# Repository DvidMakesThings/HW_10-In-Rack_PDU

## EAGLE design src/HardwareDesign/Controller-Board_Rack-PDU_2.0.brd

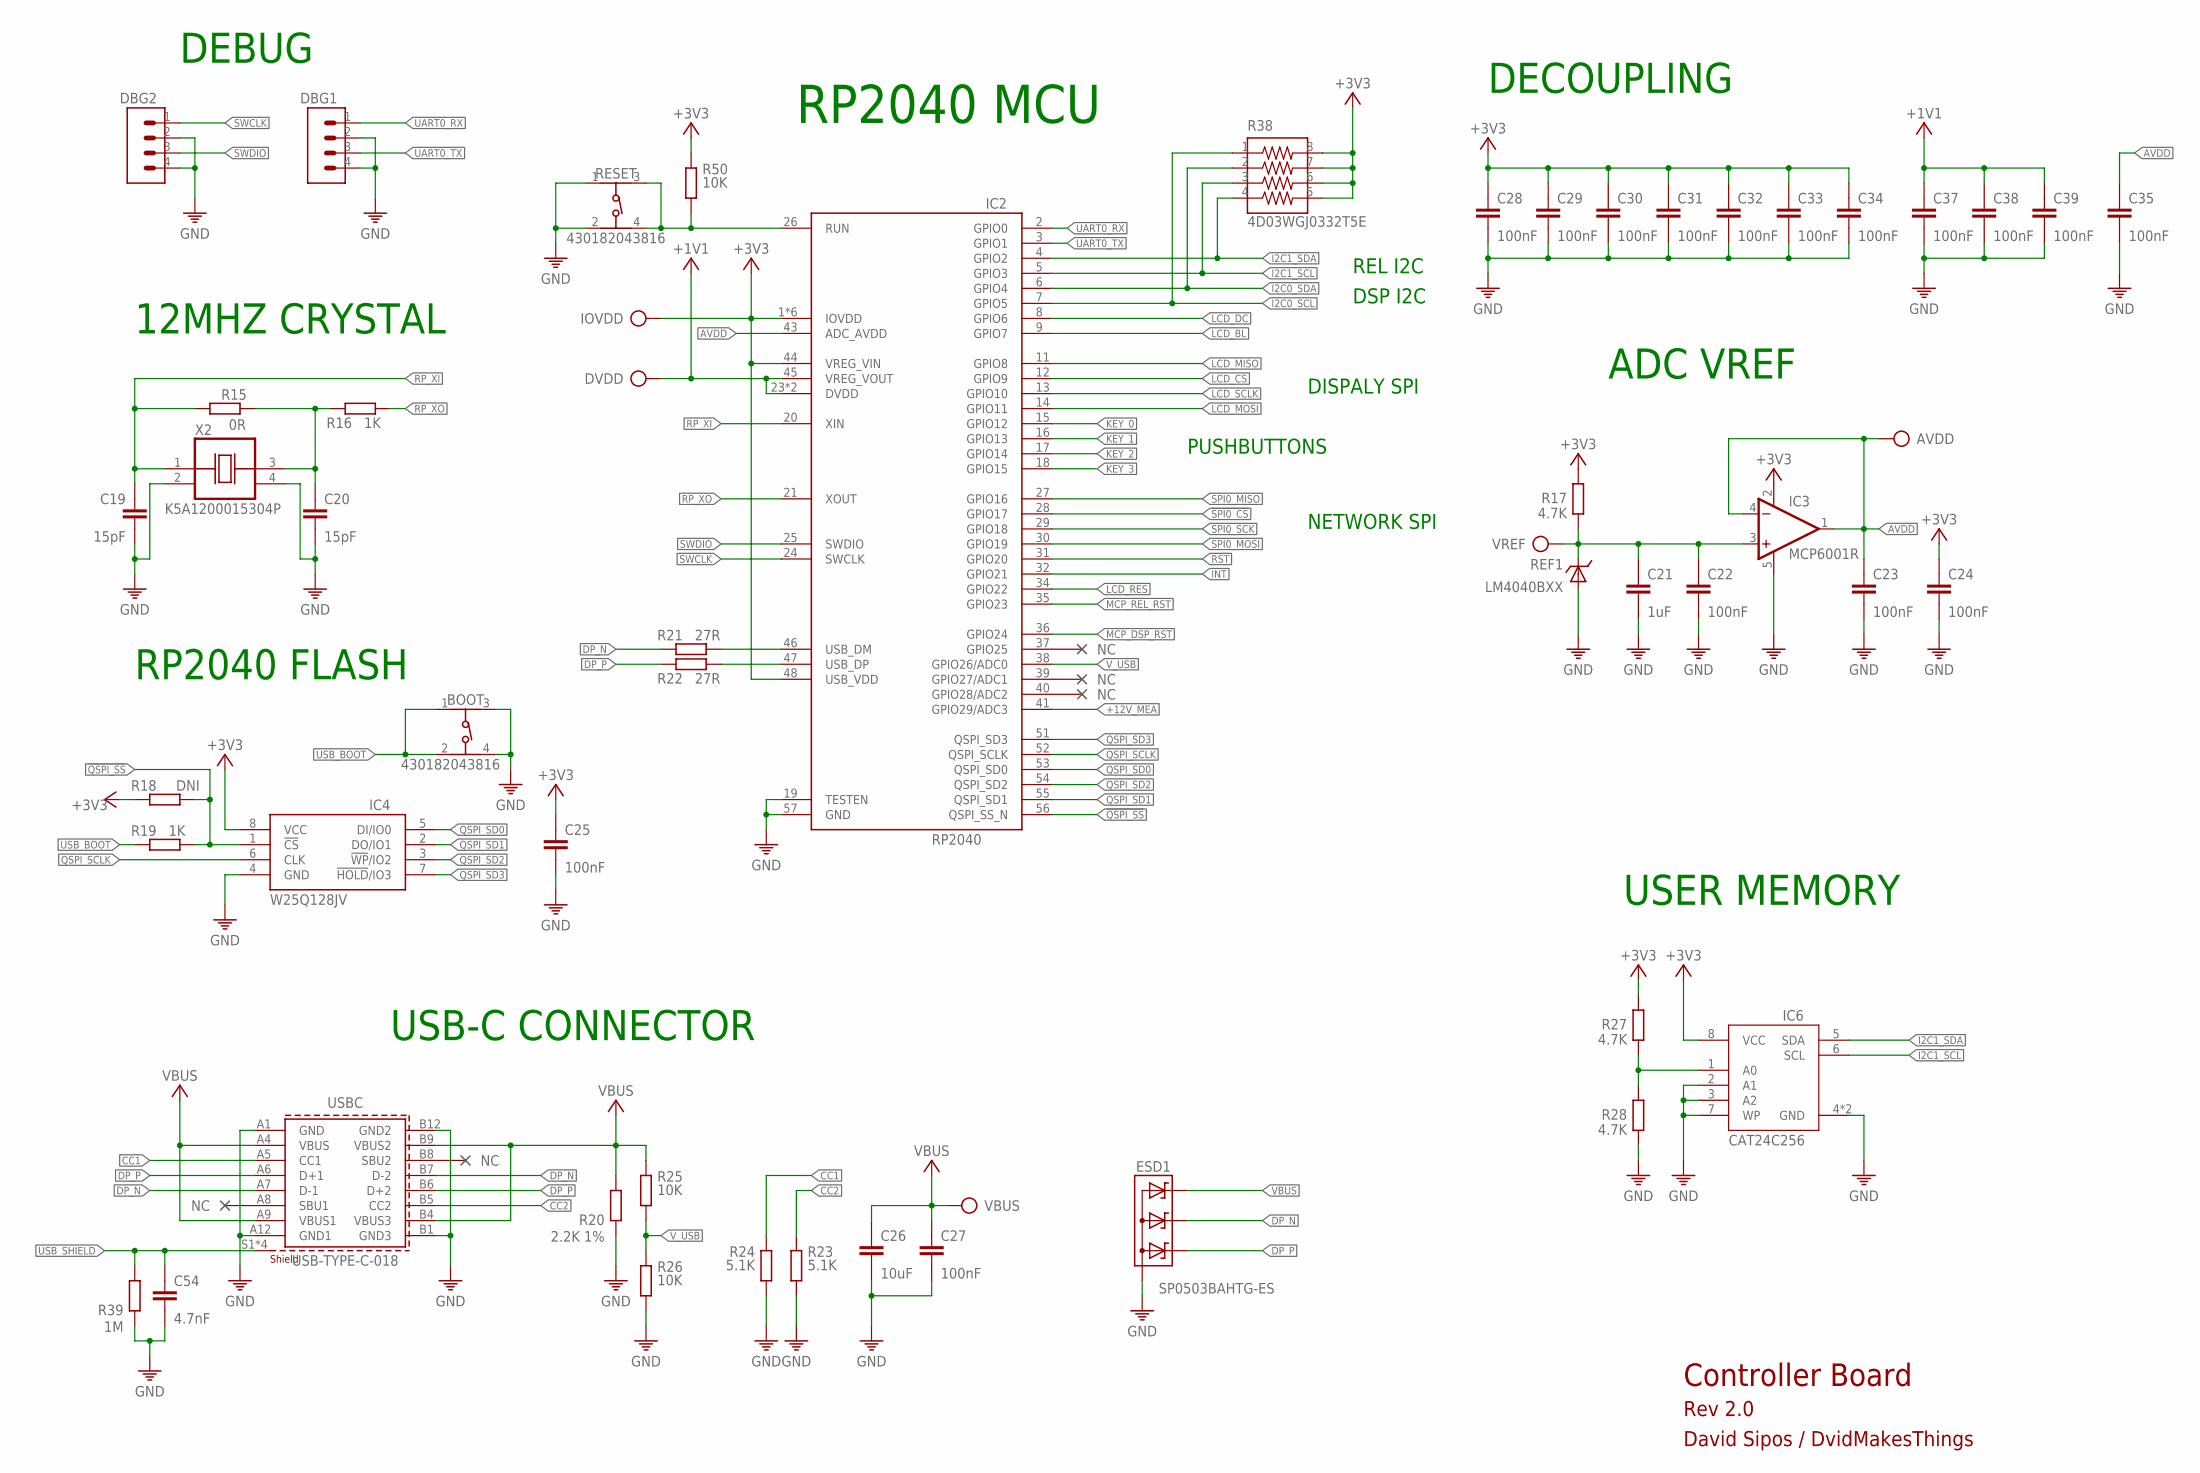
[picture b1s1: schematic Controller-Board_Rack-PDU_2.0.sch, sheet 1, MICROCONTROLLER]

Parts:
AVDD: TP
BOOT: 430182043816
C19, C20: 15pF; C0402
C21: 1uF; C0402
C22, C23, C24, C25, C28, C29, C30, C31, C32, C33, C34, C35, C37, C38, C39: 100nF; C0402
C26: 10uF; 0805
C27: 100nF; 0402
C54: 4.7nF; 0402
DBG1, DBG2: CON-1X4; 1X4
DVDD: TP
ESD1: SP0503BAHTG-ES; SOT143
IC2: RP2040; QFN40P700X700X100-57T510
IC3: MCP6001R; SOT23-5
IC4: W25Q128JVPIQ; SON127P600X500X75-8N
IC6: CAT24C256HU4IGT3; SON50P300X200X50-9T130X140N
IOVDD: TP
R15: 0R; 0402
R16, R19: 1K; 0402
R17, R27, R28: 4.7K; 0402
R18: DNI; 0402
R20: 2.2K 1%; 0402
R21, R22: 27R; 0402
R23, R24: 5.1K; 0402
R25, R26, R50: 10K; 0402
R38: 4D03WGJ0332T5E; 742C083103JP
R39: 1M; 0402
REF1: LM4040BXX; SOT23
RESET: 430182043816
USBC: USB-TYPE-C-018; 629722000214
VBUS: TP
VREF: TP
X2: K5A1200015304P; OSCCC500X320X130

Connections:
!INT: IC2.32 (GPIO21); also elsewhere on the board
!QSPI_SS: IC2.56 (QSPI_SS_N), IC4.1 (!CS), R18.1, R19.2
!RST: IC2.31 (GPIO20); also elsewhere on the board
!SPI0_CS: IC2.28 (GPIO17); also elsewhere on the board
+1V1: C37.1, C38.1, C39.1, DVDD.TP, IC2.23 (DVDD), IC2.45 (VREG_VOUT), IC2.50 (DVDD)
+3V3: C24.1, C25.1, C28.1, C29.1, C30.1, C31.1, C32.1, C33.1, C34.1, IC2.1 (IOVDD), IC2.10 (IOVDD), IC2.22 (IOVDD), IC2.33 (IOVDD), IC2.42 (IOVDD), IC2.44 (VREG_VIN), IC2.48 (USB_VDD), IC2.49 (IOVDD), IC3.2 (V+), IC4.8 (VCC), IC6.8 (VCC), IOVDD.TP, R17.2, R18.2, R27.2, R38.5, R38.6, R38.7, R38.8, R50.1; also elsewhere on the board
+12V_MEA: IC2.41 (GPIO29/ADC3); also elsewhere on the board
AVDD: AVDD.TP, C23.1, C35.1, IC2.43 (ADC_AVDD), IC3.1 (OUT), IC3.4 (-IN)
CC1: R24.1, USBC.A5 (CC1)
CC2: R23.1, USBC.B5 (CC2)
DP_N: ESD1.3 (C2), R21.1, USBC.A7 (D-1), USBC.B7 (D-2)
DP_P: ESD1.2 (C1), R22.1, USBC.A6 (D+1), USBC.B6 (D+2)
GND: BOOT.3, BOOT.4, C19.2, C20.2, C21.2, C22.2, C23.2, C24.2, C25.2, C26.2, C27.2, C28.2, C29.2, C30.2, C31.2, C32.2, C33.2, C34.2, C35.2, C37.2, C38.2, C39.2, C54.2, DBG1.2, DBG1.4, DBG2.2, DBG2.4, ESD1.1 (A), IC2.19 (TESTEN), IC2.57 (GND), IC3.5 (V-), IC4.4 (GND), IC6.2 (A1), IC6.3 (A2), IC6.4 (GND), IC6.7 (WP), IC6.9 (GND), R20.2, R23.2, R24.2, R26.2, R28.1, R39.2, REF1.2 (A), REF1.3 (A), RESET.1, RESET.2, USBC.A1 (GND), USBC.A12 (GND1), USBC.B1 (GND3), USBC.B12 (GND2), X2.2 (VSS), X2.4 (VDD); also elsewhere on the board
I2C0_SCL: IC2.7 (GPIO5), R38.1; also elsewhere on the board
I2C0_SDA: IC2.6 (GPIO4), R38.2; also elsewhere on the board
I2C1_SCL: IC2.5 (GPIO3), IC6.6 (SCL), R38.3; also elsewhere on the board
I2C1_SDA: IC2.4 (GPIO2), IC6.5 (SDA), R38.4; also elsewhere on the board
KEY_0: IC2.15 (GPIO12); also elsewhere on the board
KEY_1: IC2.16 (GPIO13); also elsewhere on the board
KEY_2: IC2.17 (GPIO14); also elsewhere on the board
KEY_3: IC2.18 (GPIO15); also elsewhere on the board
LCD_BL: IC2.9 (GPIO7); also elsewhere on the board
LCD_CS: IC2.12 (GPIO9); also elsewhere on the board
LCD_DC: IC2.8 (GPIO6); also elsewhere on the board
LCD_MISO: IC2.11 (GPIO8); also elsewhere on the board
LCD_MOSI: IC2.14 (GPIO11); also elsewhere on the board
LCD_RES: IC2.34 (GPIO22); also elsewhere on the board
LCD_SCLK: IC2.13 (GPIO10); also elsewhere on the board
MCP_DSP_RST: IC2.36 (GPIO24); also elsewhere on the board
MCP_REL_RST: IC2.35 (GPIO23); also elsewhere on the board
unnamed: C20.1, R15.2, R16.1, X2.3 (OUT)
unnamed: IC2.26 (RUN), R50.2, RESET.3, RESET.4
unnamed: IC6.1 (A0), R27.1, R28.2
QSPI_SCLK: IC2.52 (QSPI_SCLK), IC4.6 (CLK)
QSPI_SD0: IC2.53 (QSPI_SD0), IC4.5 (DI/IO0)
QSPI_SD1: IC2.55 (QSPI_SD1), IC4.2 (DO/IO1)
QSPI_SD2: IC2.54 (QSPI_SD2), IC4.3 (!WP!/IO2)
QSPI_SD3: IC2.51 (QSPI_SD3), IC4.7 (!HOLD!/IO3)
RP_XI: C19.1, IC2.20 (XIN), R15.1, X2.1 (CON)
RP_XO: IC2.21 (XOUT), R16.2
SPI0_MISO: IC2.27 (GPIO16); also elsewhere on the board
SPI0_MOSI: IC2.30 (GPIO19); also elsewhere on the board
SPI0_SCK: IC2.29 (GPIO18); also elsewhere on the board
SWCLK: DBG2.1, IC2.24 (SWCLK)
SWDIO: DBG2.3, IC2.25 (SWDIO)
UART0_RX: DBG1.1, IC2.2 (GPIO0); also elsewhere on the board
UART0_TX: DBG1.3, IC2.3 (GPIO1); also elsewhere on the board
USB_BOOT: BOOT.1, BOOT.2, R19.1
USB_DP_N: IC2.46 (USB_DM), R21.2
USB_DP_P: IC2.47 (USB_DP), R22.2
USB_SHIELD: C54.1, R39.1, USBC.S1 (SHIELD), USBC.S2 (SHIELD), USBC.S3 (SHIELD), USBC.S4 (SHIELD)
VBUS: C26.1, C27.1, ESD1.4 (C3), R20.1, R25.1, USBC.A4 (VBUS), USBC.A9 (VBUS1), USBC.B4 (VBUS3), USBC.B9 (VBUS2), VBUS.TP; also elsewhere on the board
VREF: C21.1, C22.1, IC3.3 (+IN), R17.1, REF1.1 (C), VREF.TP
V_USB: IC2.38 (GPIO26/ADC0), R25.2, R26.1

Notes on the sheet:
USB-C CONNECTOR
DECOUPLING
12MHZ CRYSTAL
RP2040 MCU
RP2040 FLASH
USER MEMORY
ADC VREF
DEBUG
Controller Board
Rev 2.0
David Sipos / DvidMakesThings
DISPALY SPI
NETWORK SPI
PUSHBUTTONS
REL I2C
DSP I2C

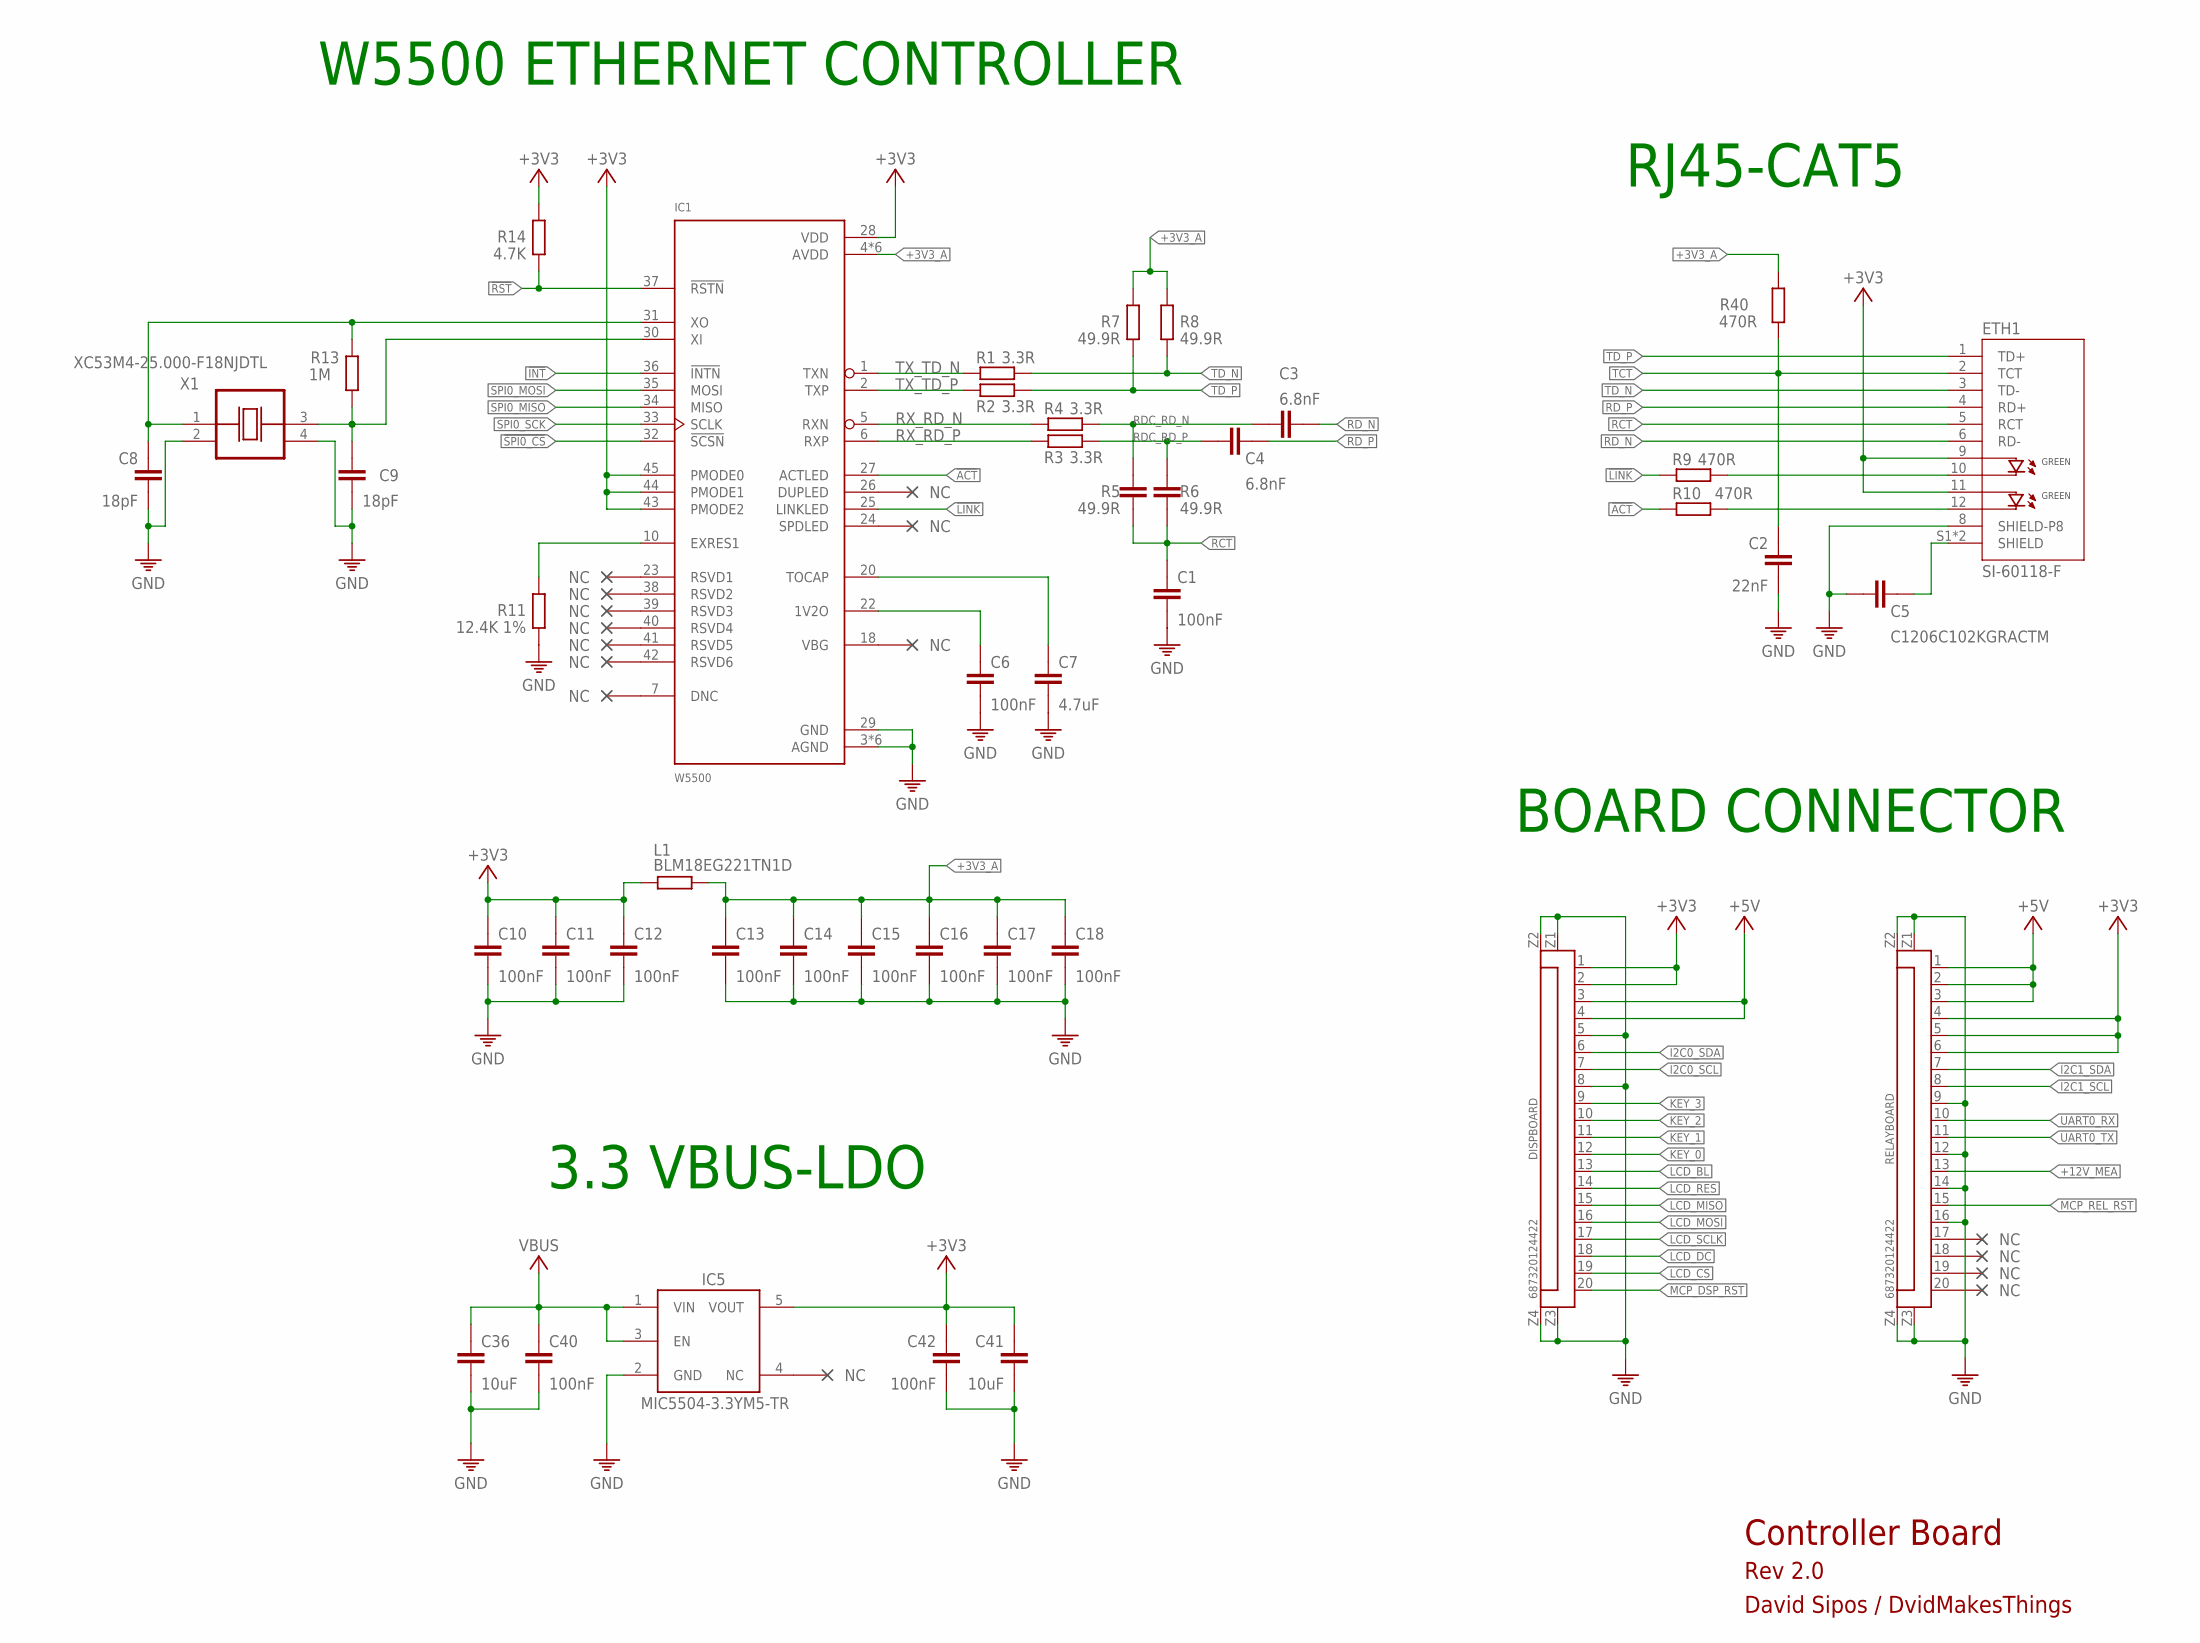
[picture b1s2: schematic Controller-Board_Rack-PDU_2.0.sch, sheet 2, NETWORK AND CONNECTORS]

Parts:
C1, C6, C10, C11, C12, C13, C14, C15, C16, C17, C18: 100nF; C0402
C2: 22nF; C0402
C3, C4: 6.8nF; C0402
C5: C1206C102KGRACTM; C1206
C7: 4.7uF; C0402
C8, C9: 18pF; C0402
C36, C41: 10uF; 0805
C40, C42: 100nF; 0402
DISPBOARD: 687320124422
ETH1: SI-60118-F; RJ45-CAT5
IC1: W5500; LQFP48
IC5: MIC5504-3.3YM5-TR; SOT23-5
L1: BLM18EG221TN1D; 0603
R1, R2, R3, R4: 3.3R; 0402
R5, R6: 49.9R; C0402
R7, R8: 49.9R; 0402
R9, R10, R40: 470R; 0402
R11: 12.4K 1%; 0402
R13: 1M; 0402
R14: 4.7K; 0402
RELAYBOARD: 687320124422
X1: XC53M4-25.000-F18NJDTL; OSCCC500X320X130

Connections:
!ACT: IC1.27 (ACTLED), R10.1
!INT: IC1.36 (!INTN); also elsewhere on the board
!LINK: IC1.25 (LINKLED), R9.1
!RST: IC1.37 (!RSTN), R14.1; also elsewhere on the board
!SPI0_CS: IC1.32 (!SCSN); also elsewhere on the board
+3V3: C10.1, C11.1, C12.1, C41.1, C42.1, DISPBOARD.1, DISPBOARD.2, ETH1.9 (GA1), ETH1.11 (GA2), IC1.28 (VDD), IC1.43 (PMODE2), IC1.44 (PMODE1), IC1.45 (PMODE0), IC5.5 (VOUT), L1.1, R14.2, RELAYBOARD.4, RELAYBOARD.5, RELAYBOARD.6; also elsewhere on the board
+3V3_A: C13.1, C14.1, C15.1, C16.1, C17.1, C18.1, IC1.4 (AVDD), IC1.8 (AVDD), IC1.11 (AVDD), IC1.15 (AVDD), IC1.17 (AVDD), IC1.21 (AVDD), L1.2, R7.2, R8.2, R40.2
+5V: DISPBOARD.3, DISPBOARD.4, RELAYBOARD.1, RELAYBOARD.2, RELAYBOARD.3
+12V_MEA: RELAYBOARD.13; also elsewhere on the board
CHASSIS: C5.2, ETH1.S1 (SHIELD), ETH1.S2 (SHIELD)
GND: C1.2, C2.2, C5.1, C6.2, C7.2, C8.2, C9.2, C10.2, C11.2, C12.2, C13.2, C14.2, C15.2, C16.2, C17.2, C18.2, C36.2, C40.2, C41.2, C42.2, DISPBOARD.5, DISPBOARD.8, DISPBOARD.Z1, DISPBOARD.Z2, DISPBOARD.Z3, DISPBOARD.Z4, ETH1.8 (SHIELD-P8), IC1.3 (AGND), IC1.9 (AGND), IC1.14 (AGND), IC1.16 (AGND), IC1.19 (AGND), IC1.29 (GND), IC1.48 (AGND), IC5.2 (GND), R11.1, RELAYBOARD.9, RELAYBOARD.12, RELAYBOARD.14, RELAYBOARD.16, RELAYBOARD.Z1, RELAYBOARD.Z2, RELAYBOARD.Z3, RELAYBOARD.Z4, X1.2 (VSS), X1.4 (VDD); also elsewhere on the board
I2C0_SCL: DISPBOARD.7; also elsewhere on the board
I2C0_SDA: DISPBOARD.6; also elsewhere on the board
I2C1_SCL: RELAYBOARD.8; also elsewhere on the board
I2C1_SDA: RELAYBOARD.7; also elsewhere on the board
KEY_0: DISPBOARD.12; also elsewhere on the board
KEY_1: DISPBOARD.11; also elsewhere on the board
KEY_2: DISPBOARD.10; also elsewhere on the board
KEY_3: DISPBOARD.9; also elsewhere on the board
LCD_BL: DISPBOARD.13; also elsewhere on the board
LCD_CS: DISPBOARD.19; also elsewhere on the board
LCD_DC: DISPBOARD.18; also elsewhere on the board
LCD_MISO: DISPBOARD.15; also elsewhere on the board
LCD_MOSI: DISPBOARD.16; also elsewhere on the board
LCD_RES: DISPBOARD.14; also elsewhere on the board
LCD_SCLK: DISPBOARD.17; also elsewhere on the board
MCP_DSP_RST: DISPBOARD.20; also elsewhere on the board
MCP_REL_RST: RELAYBOARD.15; also elsewhere on the board
unnamed: IC1.10 (EXRES1), R11.2
unnamed: ETH1.10 (GK1), R9.2
unnamed: ETH1.12 (GK2), R10.2
unnamed: C6.1, IC1.22 (1V2O)
unnamed: C7.1, IC1.20 (TOCAP)
unnamed: C9.1, IC1.30 (XI), R13.1, X1.3 (OUT)
RCT: C1.1, ETH1.5 (RCT), R5.1, R6.1
RDC_RD_N: C3.1, R4.2, R5.2
RDC_RD_P: C4.1, R3.2, R6.2
RD_N: C3.2, ETH1.6 (RD-)
RD_P: C4.2, ETH1.4 (RD+)
RX_RD_N: IC1.5 (RXN), R4.1
RX_RD_P: IC1.6 (RXP), R3.1
SPI0_MISO: IC1.34 (MISO); also elsewhere on the board
SPI0_MOSI: IC1.35 (MOSI); also elsewhere on the board
SPI0_SCK: IC1.33 (SCLK); also elsewhere on the board
TCT: C2.1, ETH1.2 (TCT), R40.1
TD_N: ETH1.3 (TD-), R1.2, R8.1
TD_P: ETH1.1 (TD+), R2.2, R7.1
TX_TD_N: IC1.1 (TXN), R1.1
TX_TD_P: IC1.2 (TXP), R2.1
UART0_RX: RELAYBOARD.10; also elsewhere on the board
UART0_TX: RELAYBOARD.11; also elsewhere on the board
VBUS: C36.1, C40.1, IC5.1 (VIN), IC5.3 (EN); also elsewhere on the board
XO: C8.1, IC1.31 (XO), R13.2, X1.1 (CON)

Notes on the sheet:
W5500 ETHERNET CONTROLLER
RJ45-CAT5
Controller Board
Rev 2.0
David Sipos / DvidMakesThings
BOARD CONNECTOR
3.3 VBUS-LDO

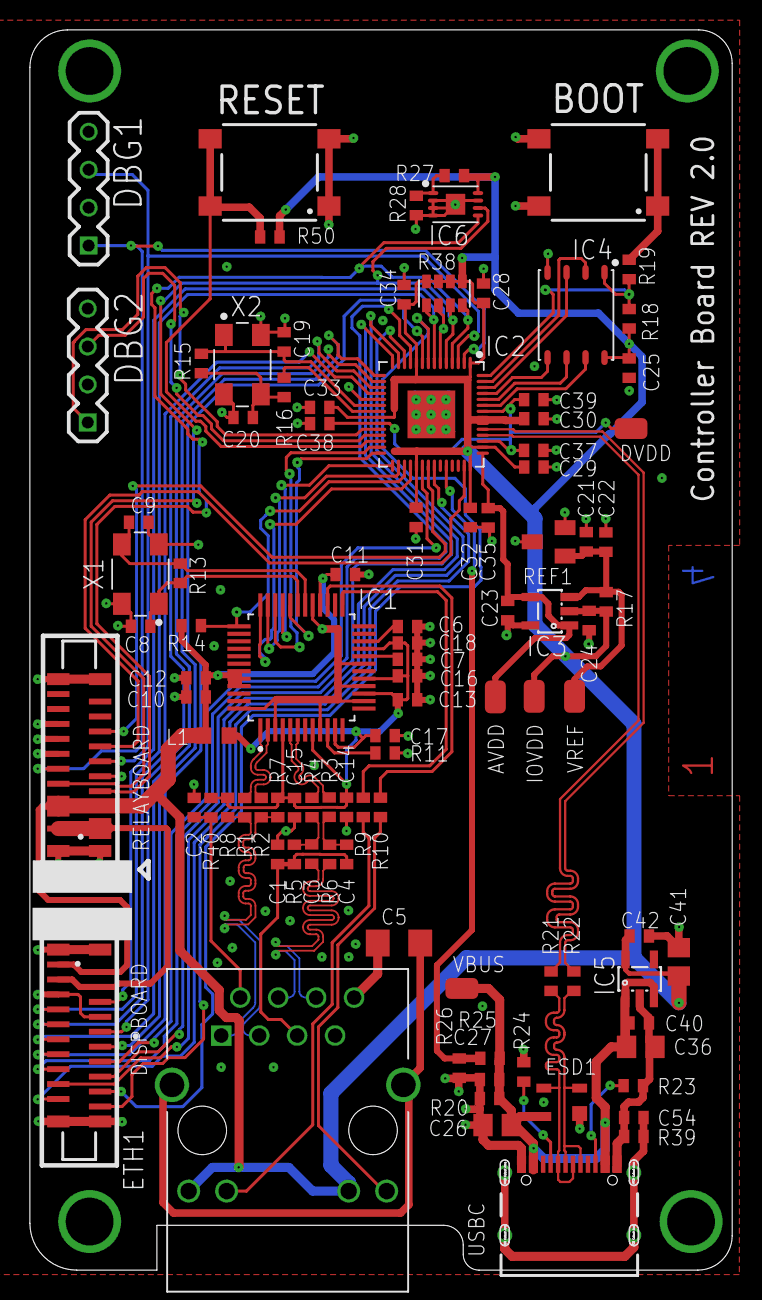
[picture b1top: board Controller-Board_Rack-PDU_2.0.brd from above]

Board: 4 copper layers, 47.0 x 83.0 mm, 99 parts (0 on the bottom side), 78 nets.

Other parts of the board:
U$1: 4-LAYER

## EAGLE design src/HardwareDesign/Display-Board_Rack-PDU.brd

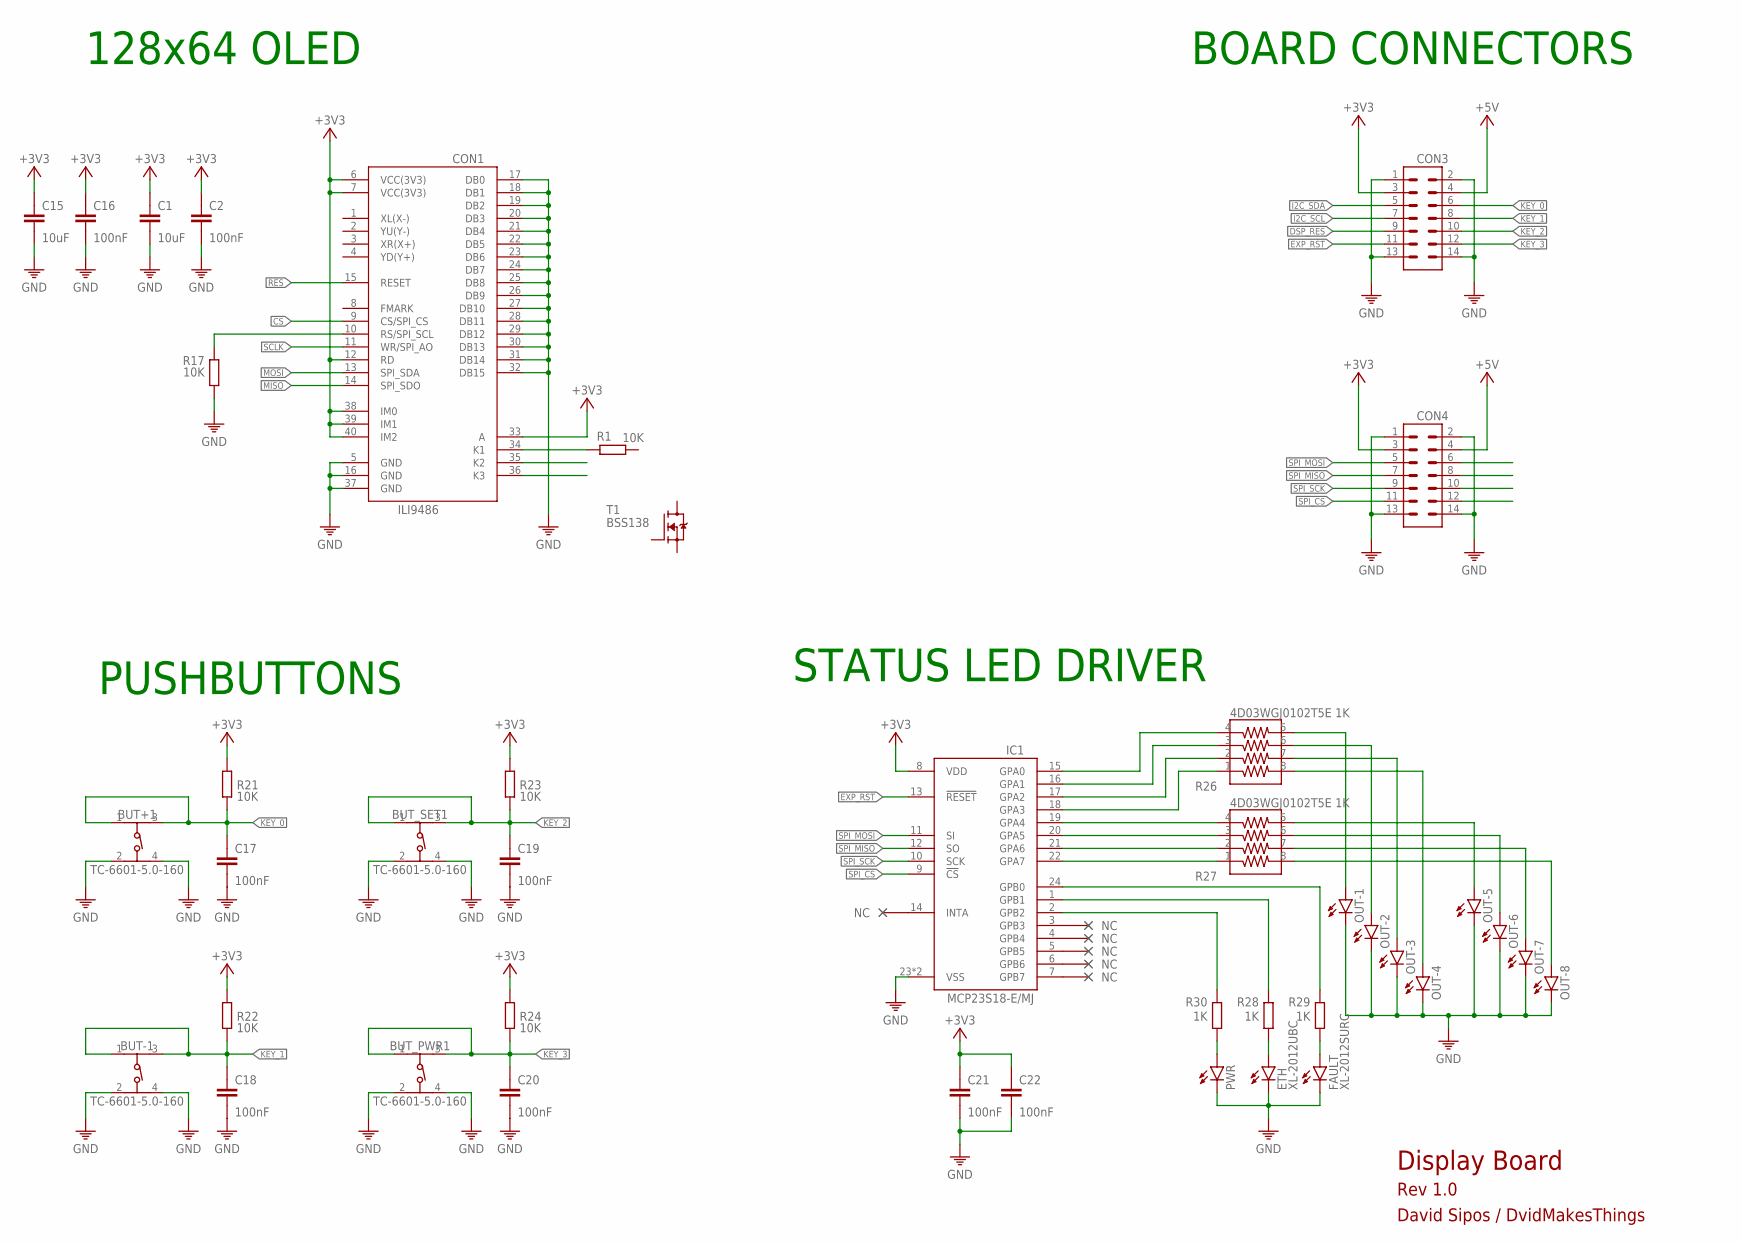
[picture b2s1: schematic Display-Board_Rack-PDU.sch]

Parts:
BUT+1: TC-6601-5.0-160; 430182043816
BUT-1: TC-6601-5.0-160; 430182043816
BUT_PWR1: TC-6601-5.0-160; 430182043816
BUT_SET1: TC-6601-5.0-160; 430182043816
C1, C15: 10uF; C0402
C2, C16, C17, C18, C19, C20, C21, C22: 100nF; C0402
CON1: 3.5IN_TFTLCD; FPC40
CON3, CON4: CON-2X72; 2X7-SIDE
ETH: XL-2012UBC; CHIP-LED0805
FAULT: XL-2012SURC; CHIP-LED0805
IC1: MCP23S18-E/MJ; QFN50P400X400X100-25T265
OUT-1, OUT-2, OUT-3, OUT-4, OUT-5, OUT-6, OUT-7, OUT-8: LEDCHIP-LED0805; CHIP-LED0805
PWR: LEDCHIP-LED0805; CHIP-LED0805
R1, R17, R21, R22, R23, R24: 10K; 0402
R26, R27: 4D03WGJ0102T5E 1K; 742C083103JP
R28, R29, R30: 1K; 0402
T1: BSS138; SOT23

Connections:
+3V3: C1.1, C2.1, C15.1, C16.1, C21.1, C22.1, CON1.6 (VCC(3V3)), CON1.7 (VCC(3V3)), CON1.12 (RD), CON1.33 (A), CON1.38 (IM0), CON1.39 (IM1), CON1.40 (IM2), CON3.3, CON4.3, IC1.8 (VDD), R21.1, R22.1, R23.1, R24.1
+5V: CON3.4, CON4.4
CS: CON1.9 (CS/SPI_CS)
DSP_RES: CON3.9
EXP_RST: CON3.11, IC1.13 (!RESET)
GND: BUT+1.2, BUT+1.4, BUT-1.2, BUT-1.4, BUT_PWR1.2, BUT_PWR1.4, BUT_SET1.2, BUT_SET1.4, C1.2, C2.2, C15.2, C16.2, C17.2, C18.2, C19.2, C20.2, C21.2, C22.2, CON1.5 (GND), CON1.16 (GND), CON1.17 (DB0), CON1.18 (DB1), CON1.19 (DB2), CON1.20 (DB3), CON1.21 (DB4), CON1.22 (DB5), CON1.23 (DB6), CON1.24 (DB7), CON1.25 (DB8), CON1.26 (DB9), CON1.27 (DB10), CON1.28 (DB11), CON1.29 (DB12), CON1.30 (DB13), CON1.31 (DB14), CON1.32 (DB15), CON1.37 (GND), CON3.1, CON3.2, CON3.13, CON3.14, CON4.1, CON4.2, CON4.13, CON4.14, ETH.C, FAULT.C, IC1.23 (VSS), IC1.25 (VSS), OUT-1.C, OUT-2.C, OUT-3.C, OUT-4.C, OUT-5.C, OUT-6.C, OUT-7.C, OUT-8.C, PWR.C, R17.1
I2C_SCL: CON3.7
I2C_SDA: CON3.5
KEY_0: BUT+1.1, BUT+1.3, C17.1, CON3.6, R21.2
KEY_1: BUT-1.1, BUT-1.3, C18.1, CON3.8, R22.2
KEY_2: BUT_SET1.1, BUT_SET1.3, C19.1, CON3.10, R23.2
KEY_3: BUT_PWR1.1, BUT_PWR1.3, C20.1, CON3.12, R24.2
MISO: CON1.14 (SPI_SDO)
MOSI: CON1.13 (SPI_SDA)
unnamed: CON1.10 (RS/SPI_SCL), R17.2
unnamed: CON1.34 (K1), R1.2
unnamed: IC1.1 (GPB1), R28.1
unnamed: IC1.2 (GPB2), R30.1
unnamed: IC1.24 (GPB0), R29.1
unnamed: IC1.15 (GPA0), R26.4
unnamed: IC1.16 (GPA1), R26.3
unnamed: IC1.17 (GPA2), R26.2
unnamed: IC1.18 (GPA3), R26.1
unnamed: IC1.19 (GPA4), R27.4
unnamed: IC1.20 (GPA5), R27.3
unnamed: IC1.21 (GPA6), R27.2
unnamed: IC1.22 (GPA7), R27.1
unnamed: OUT-1.A, R26.5
unnamed: OUT-2.A, R26.6
unnamed: OUT-3.A, R26.7
unnamed: OUT-4.A, R26.8
unnamed: OUT-5.A, R27.5
unnamed: OUT-6.A, R27.6
unnamed: OUT-7.A, R27.7
unnamed: OUT-8.A, R27.8
unnamed: FAULT.A, R29.2
unnamed: ETH.A, R28.2
unnamed: PWR.A, R30.2
RES: CON1.15 (RESET)
SCLK: CON1.11 (WR/SPI_AO)
SPI_CS: CON4.11, IC1.9 (!CS)
SPI_MISO: CON4.7, IC1.12 (SO)
SPI_MOSI: CON4.5, IC1.11 (SI)
SPI_SCK: CON4.9, IC1.10 (SCK)

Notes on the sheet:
BOARD CONNECTORS
128x64 OLED
PUSHBUTTONS
STATUS LED DRIVER
Display Board
Rev 1.0
David Sipos / DvidMakesThings

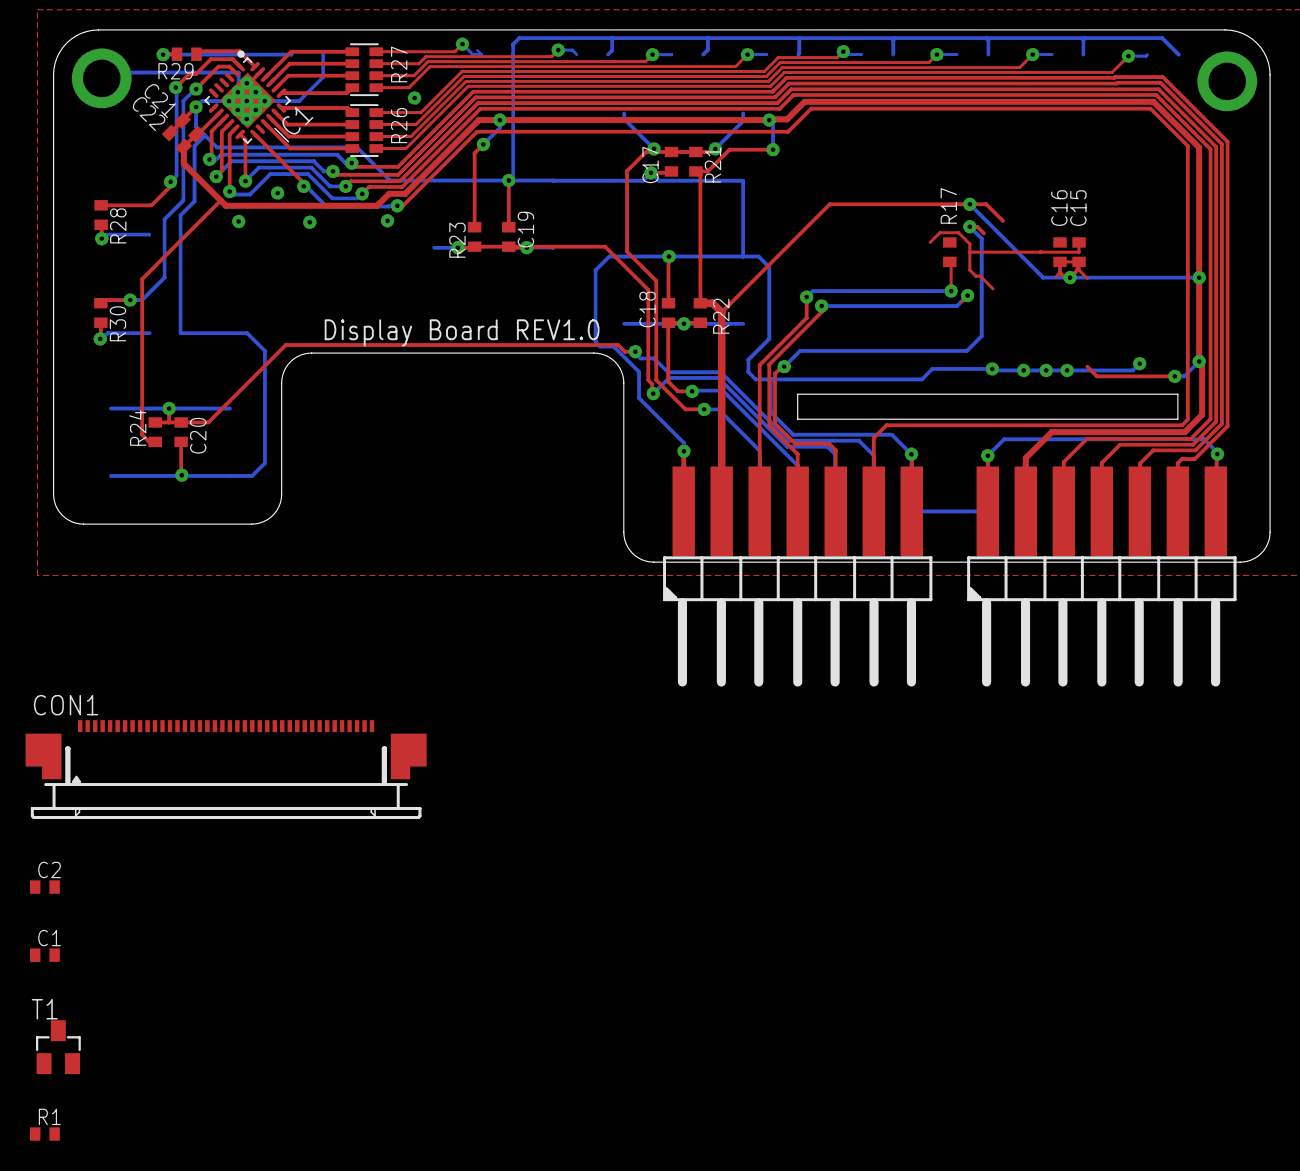
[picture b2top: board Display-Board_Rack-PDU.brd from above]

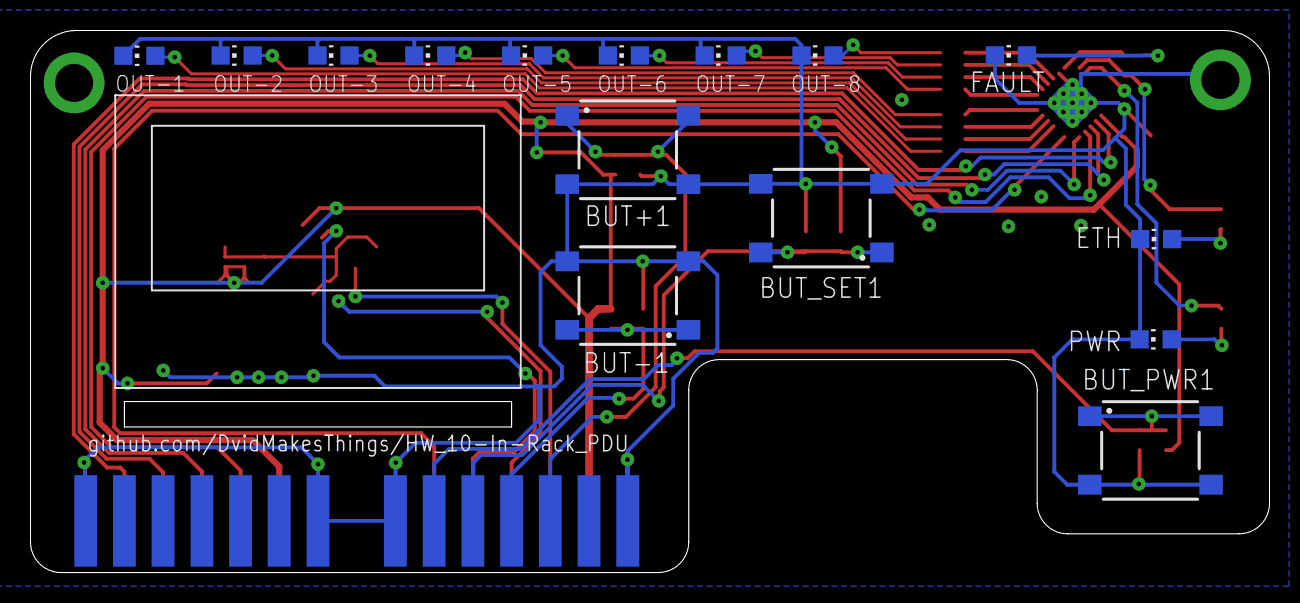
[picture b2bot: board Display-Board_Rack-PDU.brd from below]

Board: 2 copper layers, 81.3 x 35.6 mm, 41 parts (15 on the bottom side), 36 nets.

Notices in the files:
parts and their libraries:
Wurth_Connectors_WR-USB: Copyright: Würth Elektronik
COPYRIGHT: Copyright (C) 2025 Ultra Librarian. All rights reserved.
